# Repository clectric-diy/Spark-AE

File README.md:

Please use these available resources:
- [Canonical Documentation](https://clectric.diy/Spark-AE/)
- [Community Wiki](https://github.com/clectric-diy/Spark-AE/wiki)
- [clectric.diy Discussions](https://github.com/orgs/clectric-diy/discussions)

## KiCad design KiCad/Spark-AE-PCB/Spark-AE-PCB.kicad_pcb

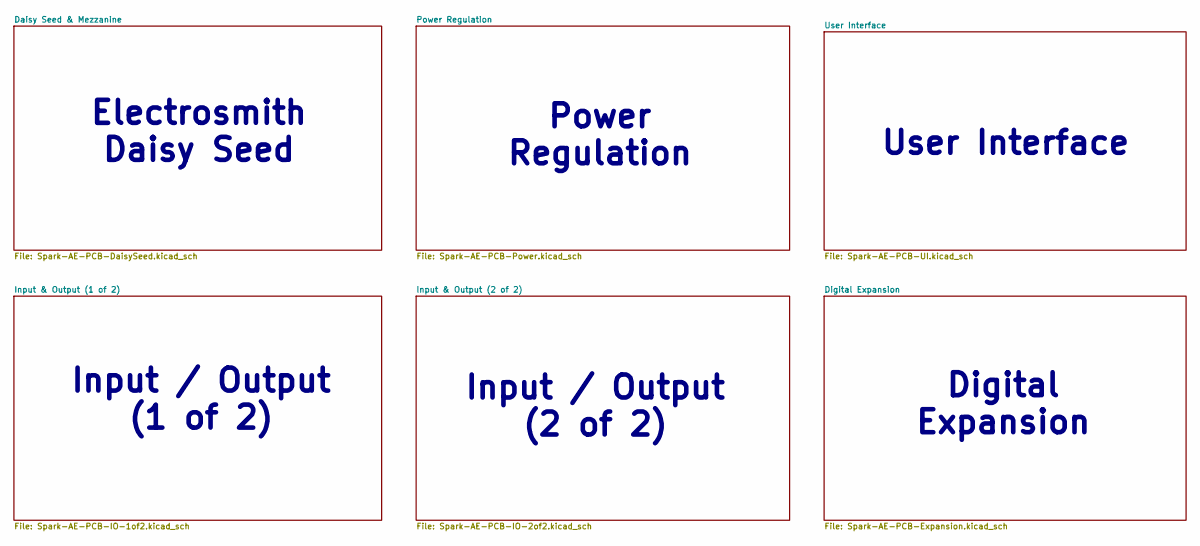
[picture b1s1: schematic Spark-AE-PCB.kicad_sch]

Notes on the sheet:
Input / Output (2 of 2)
Digital Expansion
User Interface
Input / Output (1 of 2)
Power Regulation
Electrosmith Daisy Seed

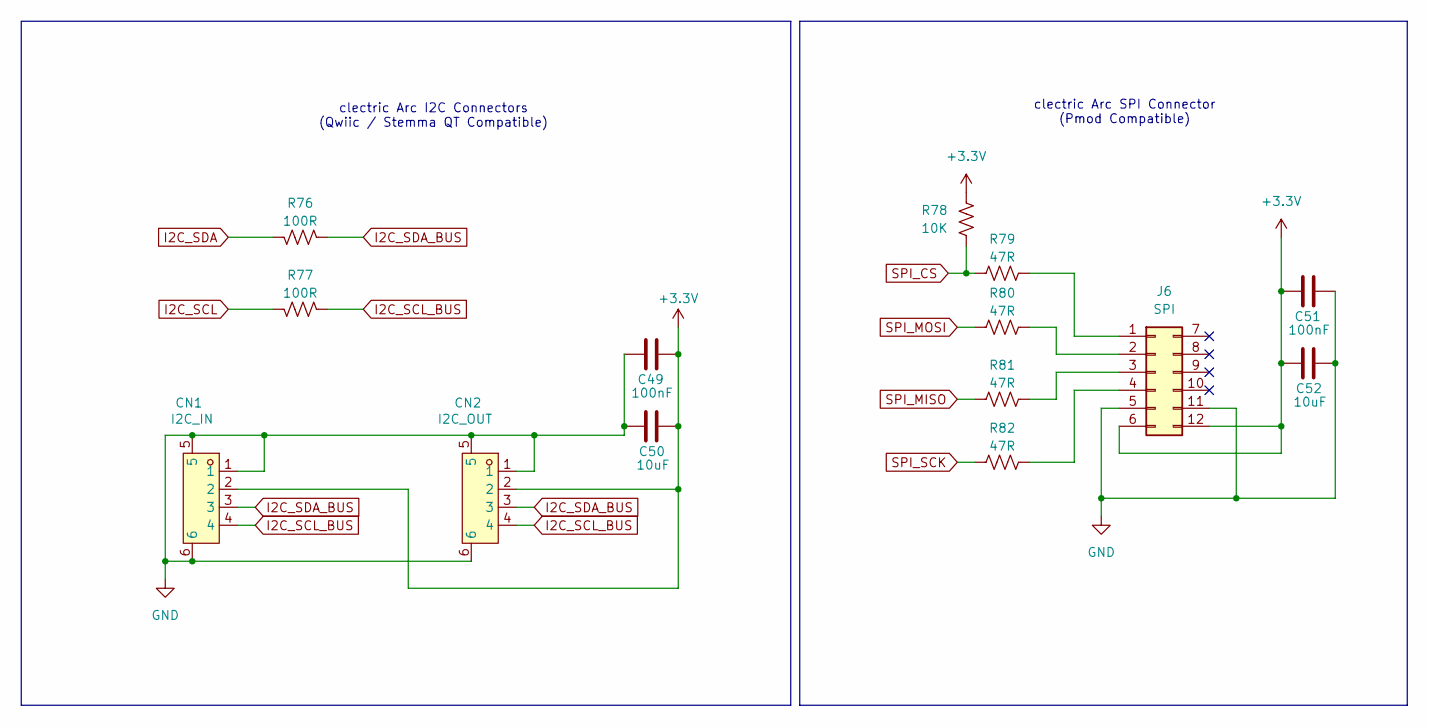
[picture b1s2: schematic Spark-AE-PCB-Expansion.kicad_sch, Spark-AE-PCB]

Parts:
C49, C51: 100nF; C_0603_1608Metric
C50, C52: 10uF; C_0603_1608Metric
CN1: I2C_IN; Connector_JST_BM04B-SRSS-TBT-LF-SN; LCSC Part C495539
CN2: I2C_OUT; Connector_JST_BM04B-SRSS-TBT-LF-SN; LCSC Part C495539
J6: SPI; PinHeader_2x06_P2.54mm_Vertical
R76, R77: 100R; R_0603_1608Metric
R78: 10K; R_0603_1608Metric
R79, R80, R81, R82: 47R; R_0603_1608Metric

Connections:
+3.3V: C49.2, C50.2, C51.1, C52.1, CN1.2, CN2.2, J6.6, J6.12, R78.1; also elsewhere on the board
GND: C49.1, C50.1, C51.2, C52.2, CN1.1, CN1.5, CN1.6, CN2.1, CN2.5, CN2.6, J6.5, J6.11; also elsewhere on the board
I2C_SCL: R77.2; also elsewhere on the board
I2C_SCL_BUS: CN1.4, CN2.4, R77.1
I2C_SDA: R76.2; also elsewhere on the board
I2C_SDA_BUS: CN1.3, CN2.3, R76.1
unnamed: J6.1, R79.2
unnamed: J6.2, R80.2
unnamed: J6.3, R81.2
unnamed: J6.4, R82.2
SPI_CS: R78.2, R79.1; also elsewhere on the board
SPI_MISO: R81.1; also elsewhere on the board
SPI_MOSI: R80.1; also elsewhere on the board
SPI_SCK: R82.1; also elsewhere on the board

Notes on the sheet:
clectric Arc SPI Connector (Pmod Compatible)
clectric Arc I2C Connectors (Qwiic / Stemma QT Compatible)

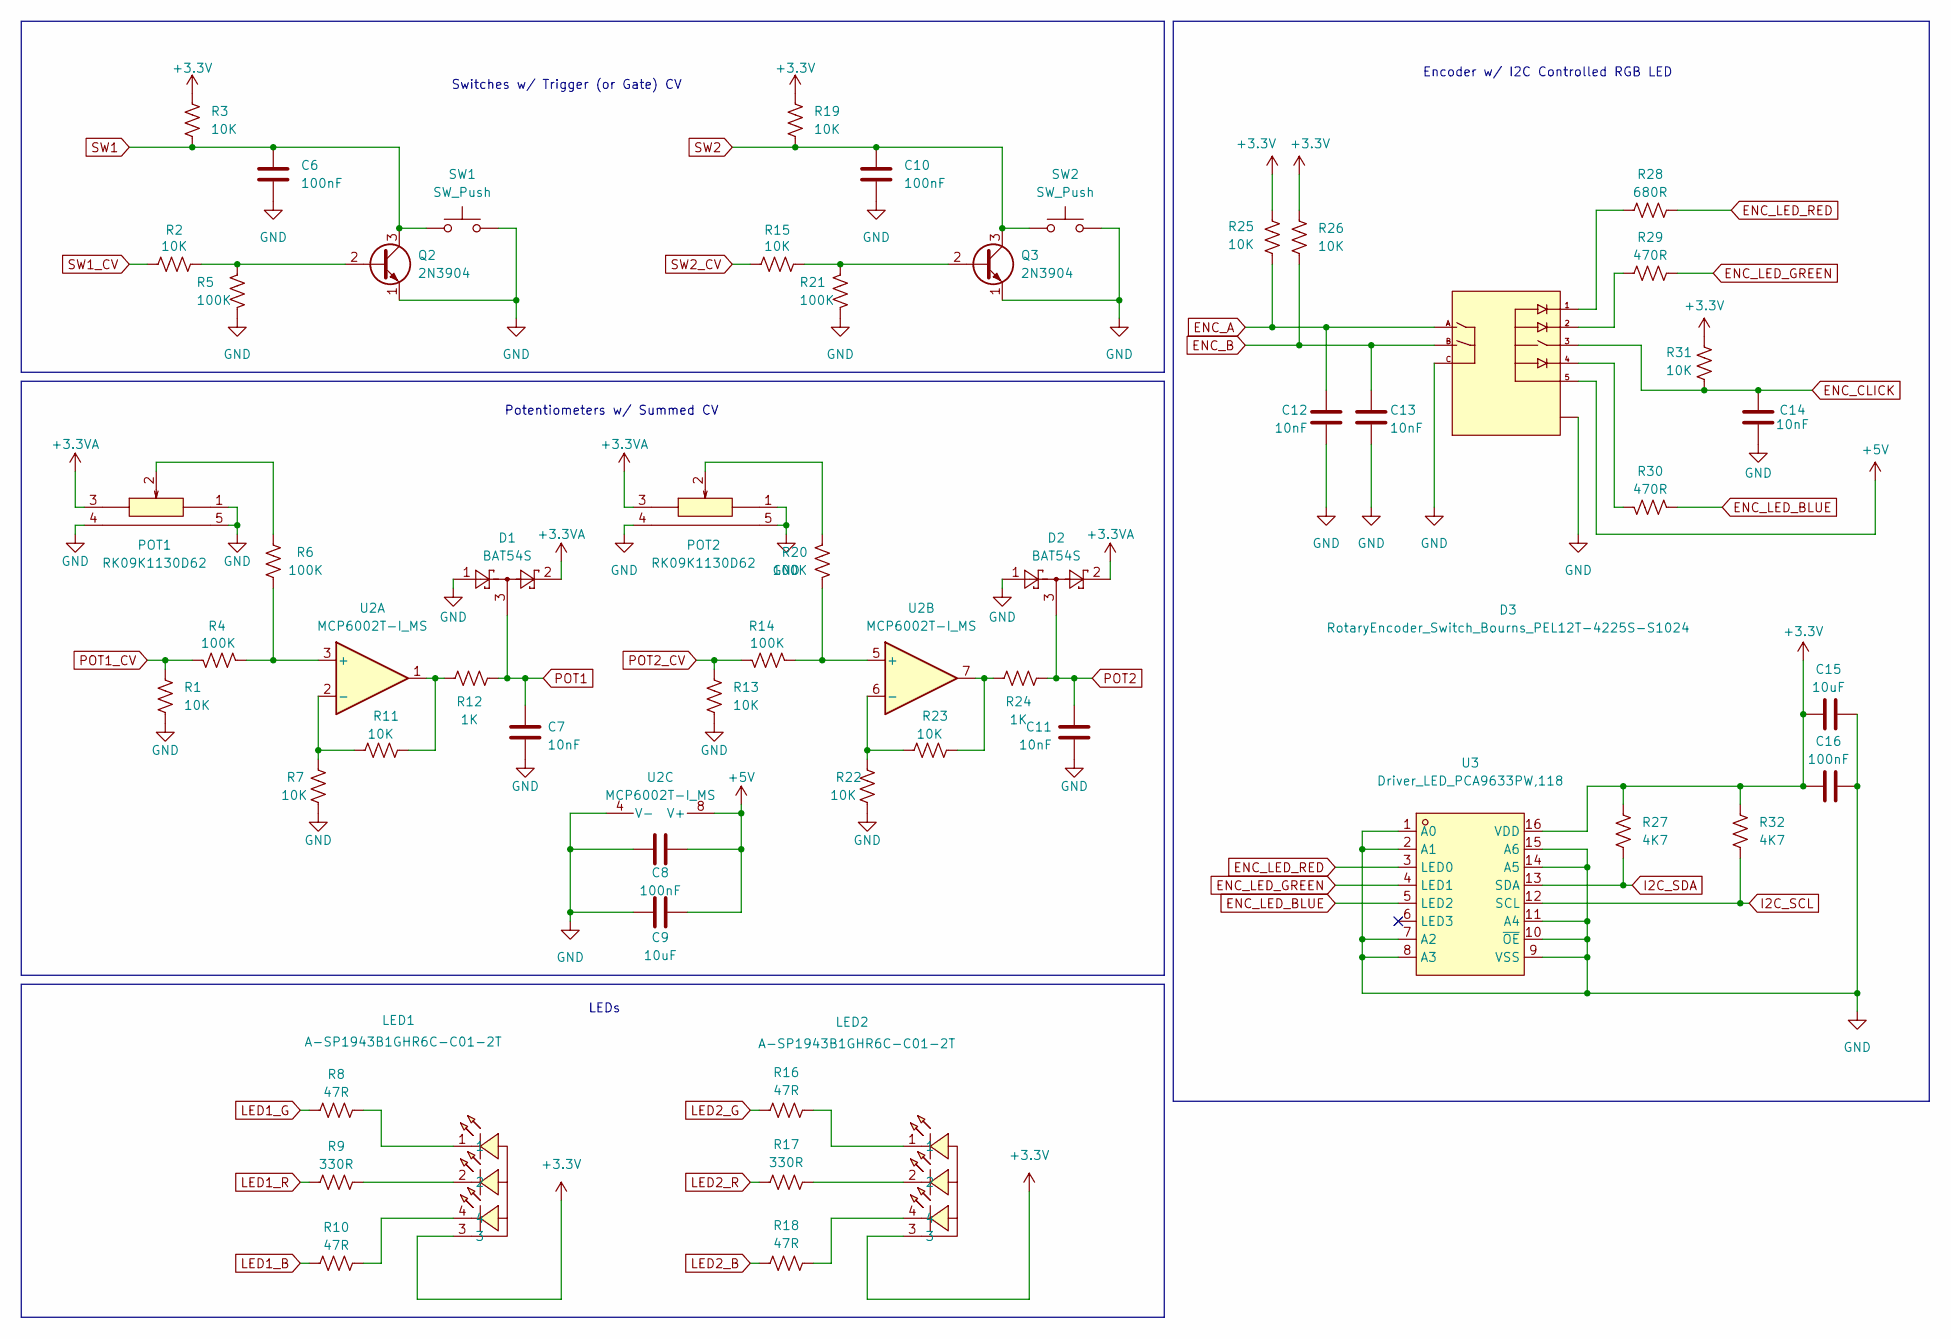
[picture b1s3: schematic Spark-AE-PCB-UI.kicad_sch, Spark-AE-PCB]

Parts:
C6, C8, C10, C16: 100nF; C_0603_1608Metric
C7, C11, C12, C13, C14: 10nF; C_0603_1608Metric
C9, C15: 10uF; C_0603_1608Metric
D1, D2: BAT54S; SOT-23
D3: RotaryEncoder_Switch_Bourns_PEL12T-4225S-S1024; PARTREV N/A
LED1, LED2: A-SP1943B1GHR6C-C01-2T; LED_ARGB_Amicc_A-SP1943B1GHR6C-C01-2T; LCSC Part C19171342
POT1, POT2: RK09K1130D62; Potentiometer_THT_Alps_RK09K1130D62; LCSC Part C470294
Q2, Q3: 2N3904; TO-92_Inline
R1, R2, R3, R7, R11, R13, R15, R19, R22, R23, R25, R26, R31: 10K; R_0603_1608Metric
R4, R5, R6, R14, R20, R21: 100K; R_0603_1608Metric
R8, R10, R16, R18: 47R; R_0603_1608Metric
R9, R17: 330R; R_0603_1608Metric
R12, R24: 1K; R_0603_1608Metric
R27, R32: 4K7; R_0603_1608Metric
R28: 680R; R_0603_1608Metric
R29, R30: 470R; R_0603_1608Metric
SW1, SW2: SW_Push; SW_PUSH_6mm
U2: MCP6002T-I_MS; Amplifier_Operational_Microchip_MCP6002T-I_MS
U3: Driver_LED_PCA9633PW,118; TSSOP-16_L5.0-W4.4-P0.64-LS6.4-BL; LCSC Part C2157802

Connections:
+3.3V: C15.1, C16.1, LED1.3, LED2.3, R3.1, R19.1, R25.1, R26.1, R27.1, R31.1, R32.1, U3.16 (VDD); also elsewhere on the board
+3.3VA: D1.2 (K), D2.2 (K), POT1.3, POT2.3; also elsewhere on the board
+5V: C8.1, C9.2, D3.5, U2.8 (V+); also elsewhere on the board
ENC_A: C12.1, D3.A, R25.2; also elsewhere on the board
ENC_B: C13.1, D3.B, R26.2; also elsewhere on the board
ENC_CLICK: C14.2, D3.3, R31.2; also elsewhere on the board
ENC_LED_BLUE: R30.1, U3.5 (LED2)
ENC_LED_GREEN: R29.2, U3.4 (LED1)
ENC_LED_RED: R28.2, U3.3 (LED0)
GND: C6.2, C7.2, C8.2, C9.1, C10.2, C11.2, C12.2, C13.2, C14.1, C15.2, C16.2, D1.1 (A), D2.1 (A), D3.C, D3.S1 (SHIELD), D3.S2 (SHIELD__1), POT1.1, POT1.4 (EH), POT1.5 (EH), POT2.1, POT2.4 (EH), POT2.5 (EH), Q2.1 (E), Q3.1 (E), R1.2, R5.2, R7.2, R13.2, R21.2, R22.2, SW1.2, SW2.2, U2.4 (V-), U3.1 (A0), U3.2 (A1), U3.7 (A2), U3.8 (A3), U3.9 (VSS), U3.10 (~OE), U3.11 (A4), U3.14 (A5), U3.15 (A6); also elsewhere on the board
I2C_SCL: R32.2, U3.12 (SCL); also elsewhere on the board
I2C_SDA: R27.2, U3.13 (SDA); also elsewhere on the board
LED1_B: R10.1; also elsewhere on the board
LED1_G: R8.1; also elsewhere on the board
LED1_R: R9.1; also elsewhere on the board
LED2_B: R18.1; also elsewhere on the board
LED2_G: R16.1; also elsewhere on the board
LED2_R: R17.1; also elsewhere on the board
unnamed: D3.1, R28.1
unnamed: D3.2, R29.1
unnamed: D3.4, R30.2
unnamed: LED1.1, R8.2
unnamed: LED1.2, R9.2
unnamed: LED1.4, R10.2
unnamed: LED2.1, R16.2
unnamed: LED2.2, R17.2
unnamed: LED2.4, R18.2
unnamed: POT1.2, R6.1
unnamed: POT2.2, R20.1
unnamed: Q2.2 (B), R2.2, R5.1
unnamed: Q3.2 (B), R15.2, R21.1
unnamed: R11.2, R12.1, U2.1
unnamed: R23.2, R24.1, U2.7
unnamed: R4.1, R6.2, U2.3 (+)
unnamed: R7.1, R11.1, U2.2 (-)
unnamed: R14.1, R20.2, U2.5 (+)
unnamed: R22.1, R23.1, U2.6 (-)
POT1: C7.1, D1.3 (COM), R12.2; also elsewhere on the board
POT1_CV: R1.1, R4.2; also elsewhere on the board
POT2: C11.1, D2.3 (COM), R24.2; also elsewhere on the board
POT2_CV: R13.1, R14.2; also elsewhere on the board
SW1: C6.1, Q2.3 (C), R3.2, SW1.1; also elsewhere on the board
SW1_CV: R2.1; also elsewhere on the board
SW2: C10.1, Q3.3 (C), R19.2, SW2.1; also elsewhere on the board
SW2_CV: R15.1; also elsewhere on the board

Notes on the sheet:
LEDs
Encoder w/ I2C Controlled RGB LED
Switches w/ Trigger (or Gate) CV
Potentiometers w/ Summed CV

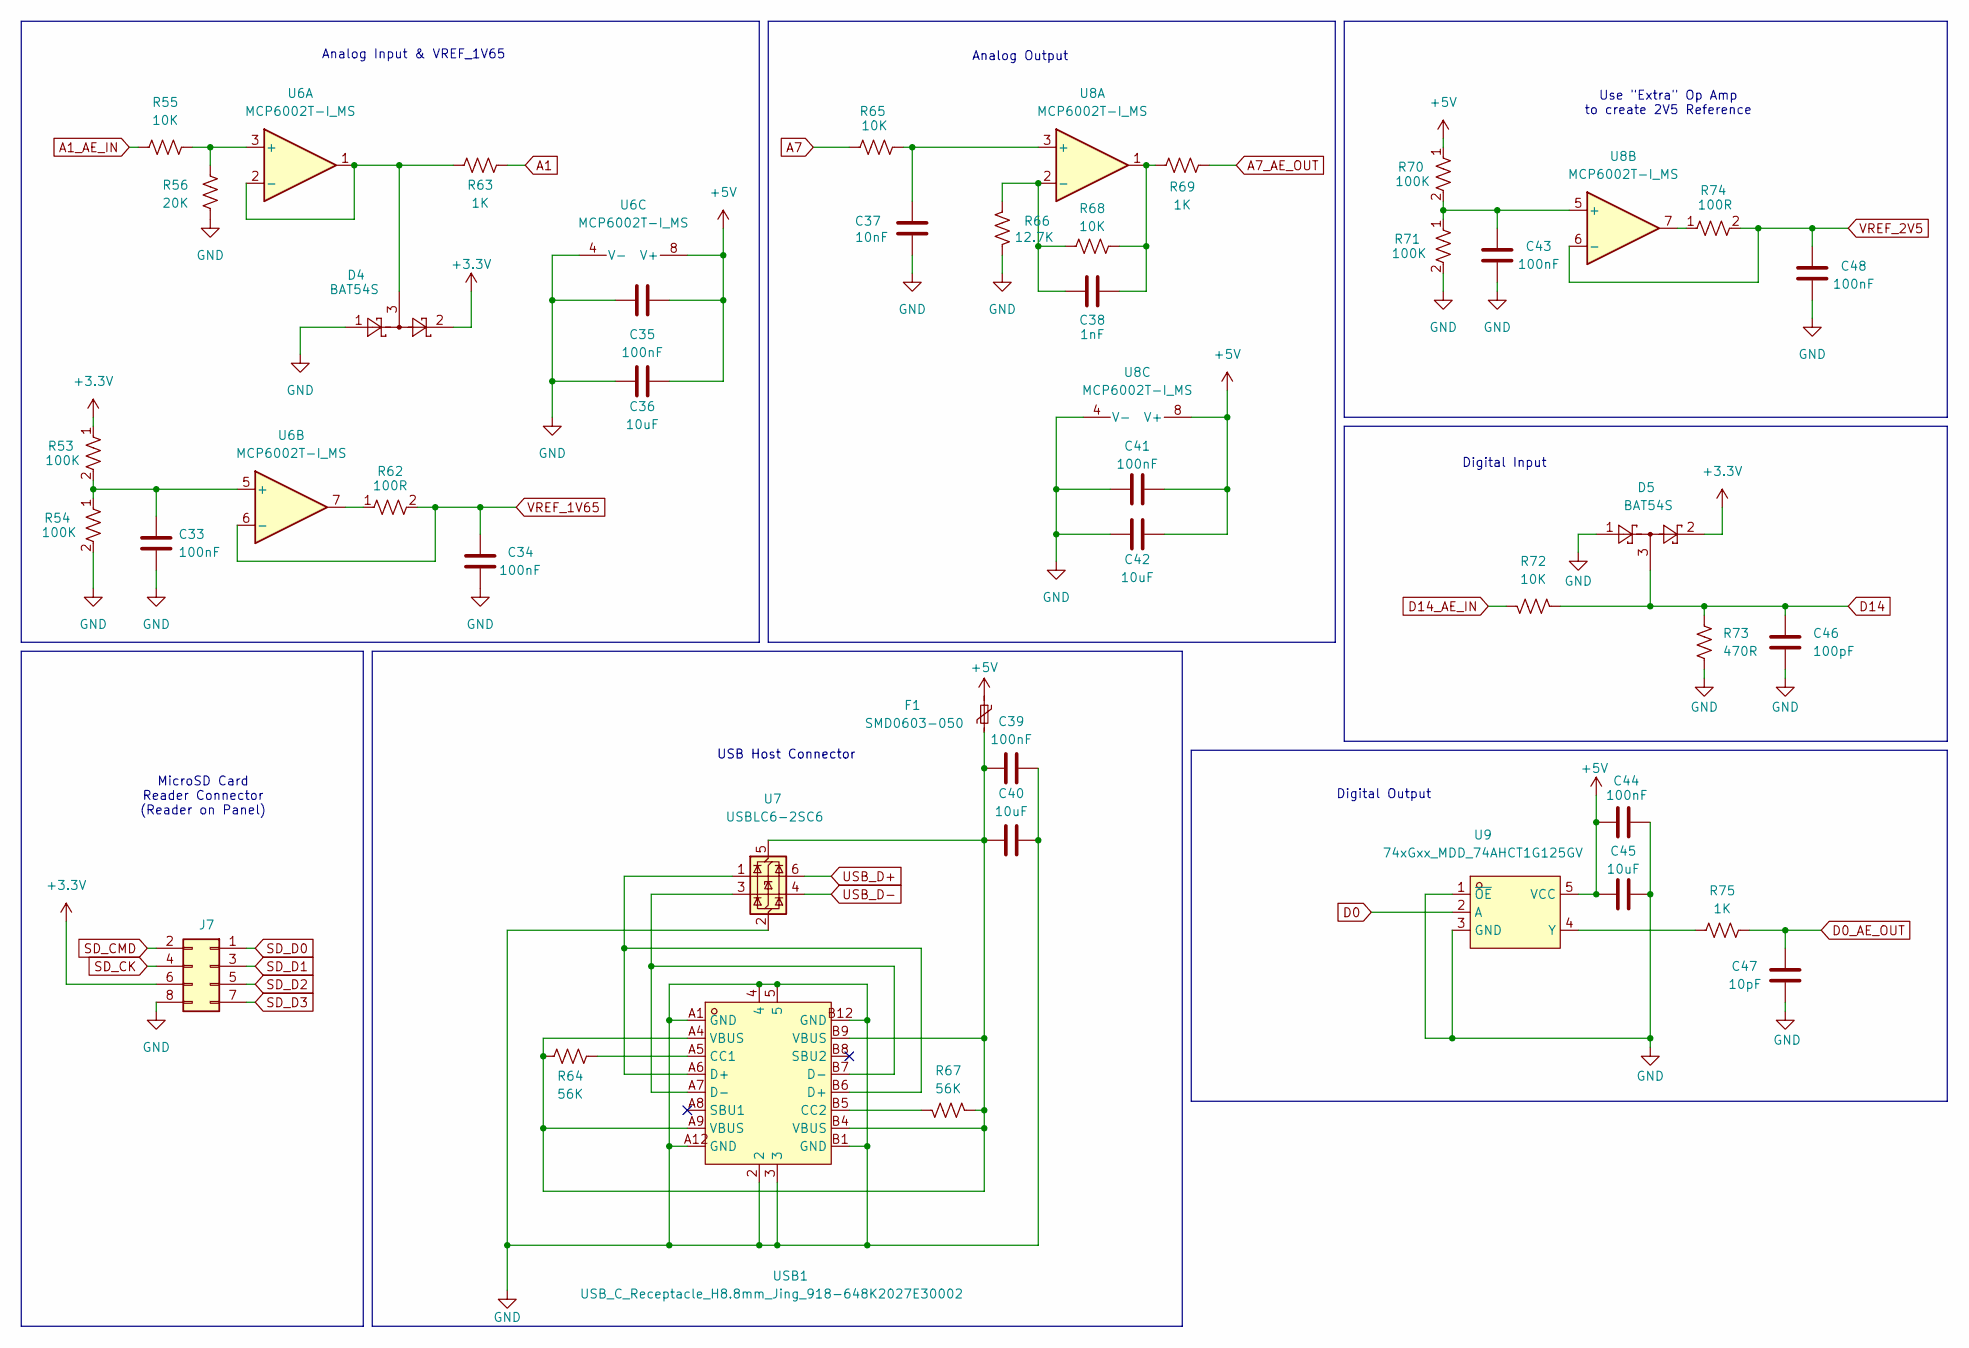
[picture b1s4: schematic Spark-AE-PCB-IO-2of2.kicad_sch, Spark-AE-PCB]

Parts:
C33, C34, C35, C39, C41, C43, C44, C48: 100nF; C_0603_1608Metric
C36, C40, C42, C45: 10uF; C_0603_1608Metric
C37: 10nF; C_0603_1608Metric
C38: 1nF; C_0603_1608Metric
C46: 100pF; C_0603_1608Metric
C47: 10pF; C_0603_1608Metric
D4, D5: BAT54S; SOT-23
F1: SMD0603-050; Fuse_0603_1608Metric
J7: SD_CONN; PinSocket_2x04_P2.54mm_Vertical
R53, R54, R70, R71: 100K; R_0603_1608Metric
R55, R65, R68, R72: 10K; R_0603_1608Metric
R56: 20K; R_0603_1608Metric
R62, R74: 100R; R_0603_1608Metric
R63, R69, R75: 1K; R_0603_1608Metric
R64, R67: 56K; R_0603_1608Metric
R66: 12.7K; R_0603_1608Metric
R73: 470R; R_0603_1608Metric
U6, U8: MCP6002T-I_MS; Amplifier_Operational_Microchip_MCP6002T-I_MS
U7: USBLC6-2SC6; SOT-23-6
U9: 74xGxx_MDD_74AHCT1G125GV; LCSC Part C52140417
USB1: USB_C_Receptacle_H8.8mm_Jing_918-648K2027E30002; LCSC Part C5139026

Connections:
+3.3V: D4.2 (K), D5.2 (K), J7.6, R53.1; also elsewhere on the board
+5V: C35.2, C36.2, C41.2, C42.2, C44.1, C45.2, F1.1, R70.1, U6.8 (V+), U8.8 (V+), U9.5 (VCC); also elsewhere on the board
A1: R63.2; also elsewhere on the board
A1_AE_IN: R55.1; also elsewhere on the board
A7: R65.1; also elsewhere on the board
A7_AE_OUT: R69.2; also elsewhere on the board
D0: U9.2 (A); also elsewhere on the board
D0_AE_OUT: C47.1, R75.1; also elsewhere on the board
D14: C46.1, D5.3 (COM), R72.2, R73.1; also elsewhere on the board
D14_AE_IN: R72.1; also elsewhere on the board
GND: C33.2, C34.2, C35.1, C36.1, C37.2, C39.2, C40.2, C41.1, C42.1, C43.2, C44.2, C45.1, C46.2, C47.2, C48.1, D4.1 (A), D5.1 (A), J7.8, R54.2, R56.2, R66.1, R71.2, R73.2, U6.4 (V-), U7.2 (GND), U8.4 (V-), U9.1 (~OE), U9.3 (GND), USB1.2, USB1.3, USB1.4, USB1.5, USB1.A1 (GND), USB1.A12 (GND), USB1.B1 (GND), USB1.B12 (GND); also elsewhere on the board
unnamed: C38.1, R68.2, R69.1, U8.1
unnamed: D4.3 (COM), R63.1, U6.1, U6.2 (-)
unnamed: R62.1, U6.7
unnamed: R74.1, U8.7
unnamed: R55.2, R56.1, U6.3 (+)
unnamed: C33.1, R53.2, R54.1, U6.5 (+)
unnamed: U7.1 (I/O1), USB1.A6 (D+), USB1.B6 (D+)
unnamed: U7.3 (I/O2), USB1.A7 (D-), USB1.B7 (D-)
unnamed: C39.1, C40.1, F1.2, R64.1, R67.1, U7.5 (VBUS), USB1.A4 (VBUS), USB1.A9 (VBUS), USB1.B4 (VBUS), USB1.B9 (VBUS)
unnamed: C37.1, R65.2, U8.3 (+)
unnamed: C38.2, R66.2, R68.1, U8.2 (-)
unnamed: C43.1, R70.2, R71.1, U8.5 (+)
unnamed: R75.2, U9.4 (Y)
unnamed: R64.2, USB1.A5 (CC1)
unnamed: R67.2, USB1.B5 (CC2)
SD_CK: J7.4; also elsewhere on the board
SD_CMD: J7.2; also elsewhere on the board
SD_D0: J7.1; also elsewhere on the board
SD_D1: J7.3; also elsewhere on the board
SD_D2: J7.5; also elsewhere on the board
SD_D3: J7.7; also elsewhere on the board
USB_D+: U7.6 (I/O1); also elsewhere on the board
USB_D-: U7.4 (I/O2); also elsewhere on the board
VREF_1V65: C34.1, R62.2, U6.6 (-); also elsewhere on the board
VREF_2V5: C48.2, R74.2, U8.6 (-); also elsewhere on the board

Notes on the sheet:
Analog Input & VREF_1V65
MicroSD Card Reader Connector (Reader on Panel)
Analog Output
Digital Input
USB Host Connector
Digital Output
Use "Extra" Op Amp to create 2V5 Reference

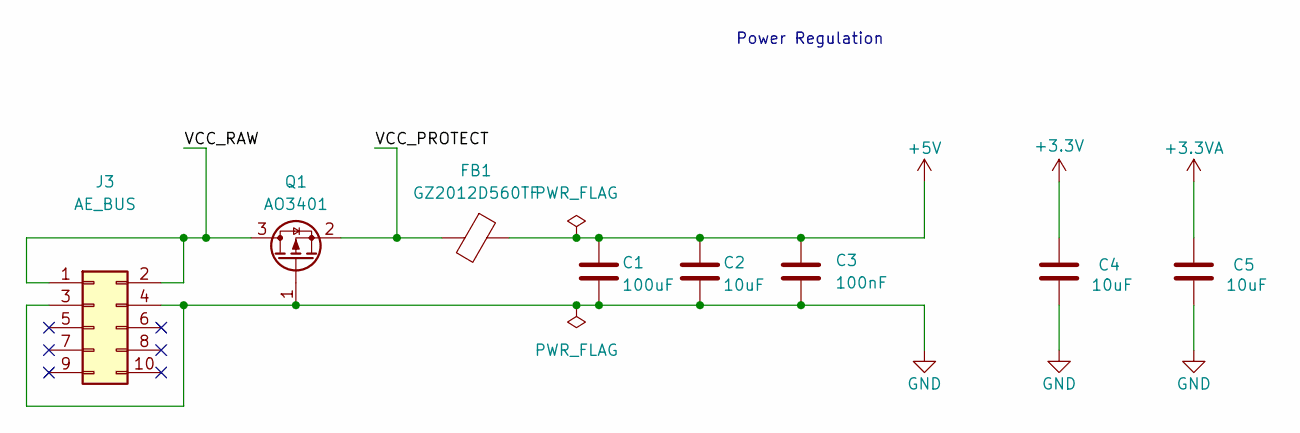
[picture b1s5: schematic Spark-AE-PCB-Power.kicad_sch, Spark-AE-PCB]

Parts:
C1: 100uF; C_0805_2012Metric
C2: 10uF; C_0805_2012Metric
C3: 100nF; C_0805_2012Metric
C4, C5: 10uF; C_0603_1608Metric
FB1: GZ2012D560TF; L_0805_2012Metric
J3: AE_BUS; PinHeader_2x05_P2.54mm_Vertical
Q1: AO3401; SOT-23

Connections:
+3.3V: C4.2; also elsewhere on the board
+3.3VA: C5.2; also elsewhere on the board
+5V: C1.1, C2.1, C3.1, FB1.1; also elsewhere on the board
/Power Regulation/VCC_PROTECT: FB1.2, Q1.2 (S)
/Power Regulation/VCC_RAW: J3.1, J3.2, Q1.3 (D)
GND: C1.2, C2.2, C3.2, C4.1, C5.1, J3.3, J3.4, Q1.1 (G); also elsewhere on the board

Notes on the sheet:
Power Regulation

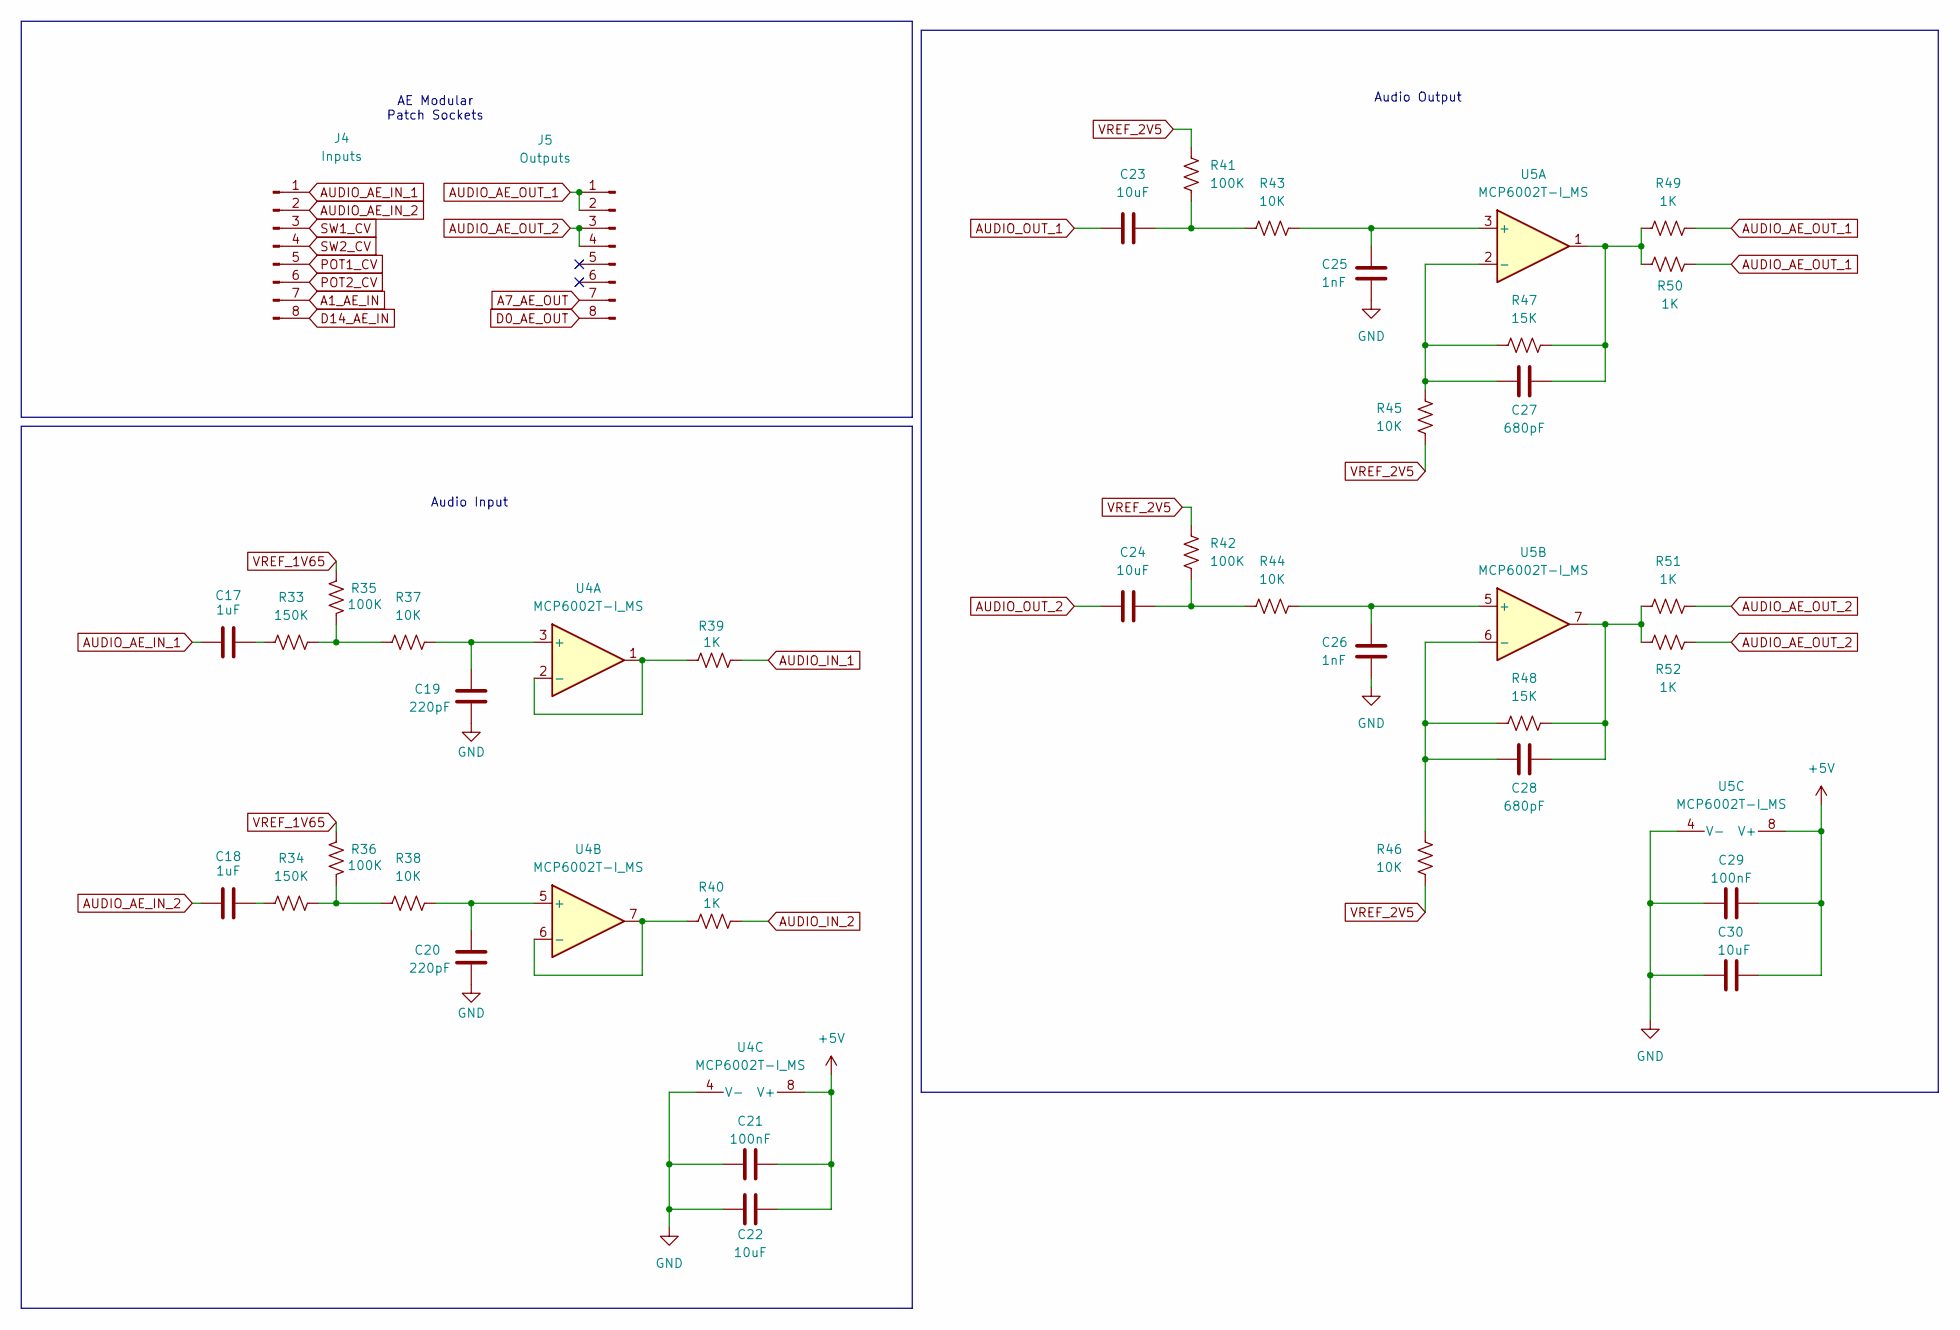
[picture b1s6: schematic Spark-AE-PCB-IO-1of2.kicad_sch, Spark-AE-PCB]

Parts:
C17, C18: 1uF; C_0603_1608Metric
C19, C20: 220pF; C_0603_1608Metric
C21, C29: 100nF; C_0603_1608Metric
C22, C23, C24, C30: 10uF; C_0603_1608Metric
C25, C26: 1nF; C_0603_1608Metric
C27, C28: 680pF; C_0603_1608Metric
J4: Inputs; Connector_PinSocket-1x08-P2.54mm-H8.5mm_Preci-Dip_801-87-00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
J5: Outputs; Connector_PinSocket-1x08-P2.54mm-H8.5mm_Preci-Dip_801-87-00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
R33, R34: 150K; R_0603_1608Metric
R35, R36, R41, R42: 100K; R_0603_1608Metric
R37, R38, R43, R44, R45, R46: 10K; R_0603_1608Metric
R39, R40, R49, R50, R51, R52: 1K; R_0603_1608Metric
R47, R48: 15K; R_0603_1608Metric
U4, U5: MCP6002T-I_MS; Amplifier_Operational_Microchip_MCP6002T-I_MS

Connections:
+5V: C21.2, C22.2, C29.2, C30.1, U4.8 (V+), U5.8 (V+); also elsewhere on the board
A1_AE_IN: J4.7; also elsewhere on the board
A7_AE_OUT: J5.7; also elsewhere on the board
AUDIO_AE_IN_1: C17.1, J4.1
AUDIO_AE_IN_2: C18.1, J4.2
AUDIO_AE_OUT_1: J5.1, J5.2, R49.2, R50.2
AUDIO_AE_OUT_2: J5.3, J5.4, R51.2, R52.2
AUDIO_IN_1: R39.1; also elsewhere on the board
AUDIO_IN_2: R40.1; also elsewhere on the board
AUDIO_OUT_1: C23.2; also elsewhere on the board
AUDIO_OUT_2: C24.2; also elsewhere on the board
D0_AE_OUT: J5.8; also elsewhere on the board
D14_AE_IN: J4.8; also elsewhere on the board
GND: C19.2, C20.2, C21.1, C22.1, C25.2, C26.2, C29.1, C30.2, U4.4 (V-), U5.4 (V-); also elsewhere on the board
unnamed: C17.2, R33.1
unnamed: C18.2, R34.1
unnamed: C23.1, R41.2, R43.1
unnamed: C24.1, R42.2, R44.1
unnamed: C27.1, R47.2, R49.1, R50.1, U5.1
unnamed: C28.1, R48.2, R51.1, R52.1, U5.7
unnamed: R33.2, R35.1, R37.1
unnamed: R34.2, R36.1, R38.1
unnamed: C19.1, R37.2, U4.3 (+)
unnamed: R39.2, U4.1, U4.2 (-)
unnamed: C20.1, R38.2, U4.5 (+)
unnamed: R40.2, U4.6 (-), U4.7
unnamed: C25.1, R43.2, U5.3 (+)
unnamed: C27.2, R45.2, R47.1, U5.2 (-)
unnamed: C26.1, R44.2, U5.5 (+)
unnamed: C28.2, R46.2, R48.1, U5.6 (-)
POT1_CV: J4.5; also elsewhere on the board
POT2_CV: J4.6; also elsewhere on the board
SW1_CV: J4.3; also elsewhere on the board
SW2_CV: J4.4; also elsewhere on the board
VREF_1V65: R35.2, R36.2; also elsewhere on the board
VREF_2V5: R41.1, R42.1, R45.1, R46.1; also elsewhere on the board

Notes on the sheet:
Audio Input
Audio Output
AE Modular Patch Sockets

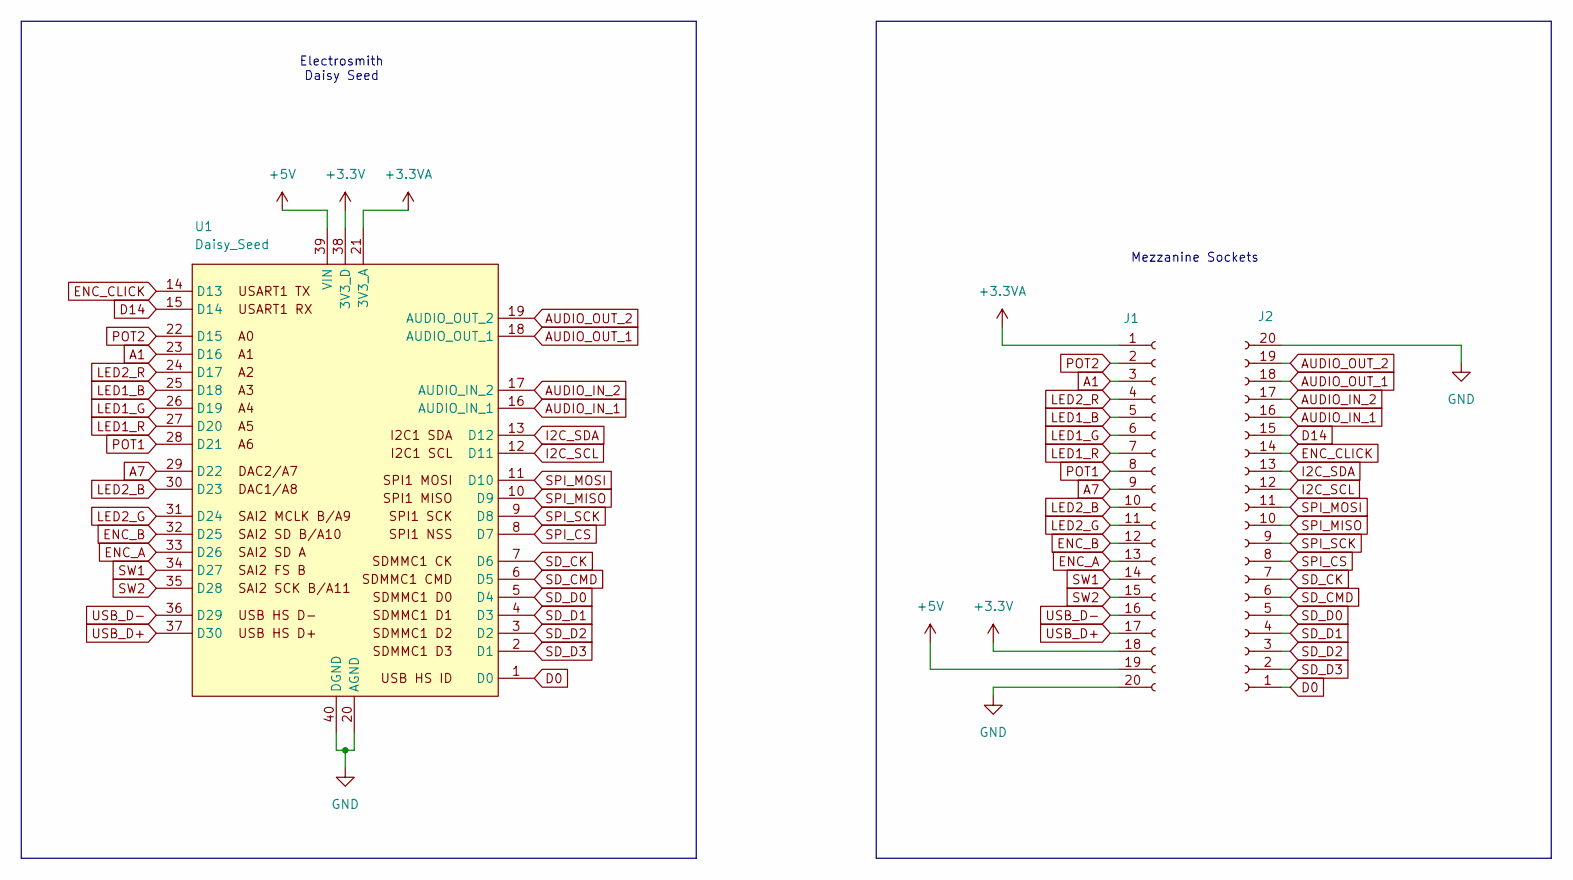
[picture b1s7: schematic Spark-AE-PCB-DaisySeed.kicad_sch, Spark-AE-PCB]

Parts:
J1, J2: Conn_01x20_Socket; Connector_PinSocket-1x20-P2.54mm-H1.27mm_Mill-Max_315-13-12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
U1: Daisy_Seed; MCU_Module_Electrosmith_DAISY_SEED

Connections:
+3.3V: J1.18, U1.38 (3V3_D); also elsewhere on the board
+3.3VA: J1.1, U1.21 (3V3_A); also elsewhere on the board
+5V: J1.19, U1.39 (VIN); also elsewhere on the board
A1: J1.3, U1.23 (D16); also elsewhere on the board
A7: J1.9, U1.29 (D22); also elsewhere on the board
AUDIO_IN_1: J2.16, U1.16 (AUDIO_IN_1); also elsewhere on the board
AUDIO_IN_2: J2.17, U1.17 (AUDIO_IN_2); also elsewhere on the board
AUDIO_OUT_1: J2.18, U1.18 (AUDIO_OUT_1); also elsewhere on the board
AUDIO_OUT_2: J2.19, U1.19 (AUDIO_OUT_2); also elsewhere on the board
D0: J2.1, U1.1 (D0); also elsewhere on the board
D14: J2.15, U1.15 (D14); also elsewhere on the board
ENC_A: J1.13, U1.33 (D26); also elsewhere on the board
ENC_B: J1.12, U1.32 (D25); also elsewhere on the board
ENC_CLICK: J2.14, U1.14 (D13); also elsewhere on the board
GND: J1.20, J2.20, U1.20 (AGND), U1.40 (DGND); also elsewhere on the board
I2C_SCL: J2.12, U1.12 (D11); also elsewhere on the board
I2C_SDA: J2.13, U1.13 (D12); also elsewhere on the board
LED1_B: J1.5, U1.25 (D18); also elsewhere on the board
LED1_G: J1.6, U1.26 (D19); also elsewhere on the board
LED1_R: J1.7, U1.27 (D20); also elsewhere on the board
LED2_B: J1.10, U1.30 (D23); also elsewhere on the board
LED2_G: J1.11, U1.31 (D24); also elsewhere on the board
LED2_R: J1.4, U1.24 (D17); also elsewhere on the board
POT1: J1.8, U1.28 (D21); also elsewhere on the board
POT2: J1.2, U1.22 (D15); also elsewhere on the board
SD_CK: J2.7, U1.7 (D6); also elsewhere on the board
SD_CMD: J2.6, U1.6 (D5); also elsewhere on the board
SD_D0: J2.5, U1.5 (D4); also elsewhere on the board
SD_D1: J2.4, U1.4 (D3); also elsewhere on the board
SD_D2: J2.3, U1.3 (D2); also elsewhere on the board
SD_D3: J2.2, U1.2 (D1); also elsewhere on the board
SPI_CS: J2.8, U1.8 (D7); also elsewhere on the board
SPI_MISO: J2.10, U1.10 (D9); also elsewhere on the board
SPI_MOSI: J2.11, U1.11 (D10); also elsewhere on the board
SPI_SCK: J2.9, U1.9 (D8); also elsewhere on the board
SW1: J1.14, U1.34 (D27); also elsewhere on the board
SW2: J1.15, U1.35 (D28); also elsewhere on the board
USB_D+: J1.17, U1.37 (D30); also elsewhere on the board
USB_D-: J1.16, U1.36 (D29); also elsewhere on the board

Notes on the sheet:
Mezzanine Sockets
Electrosmith Daisy Seed

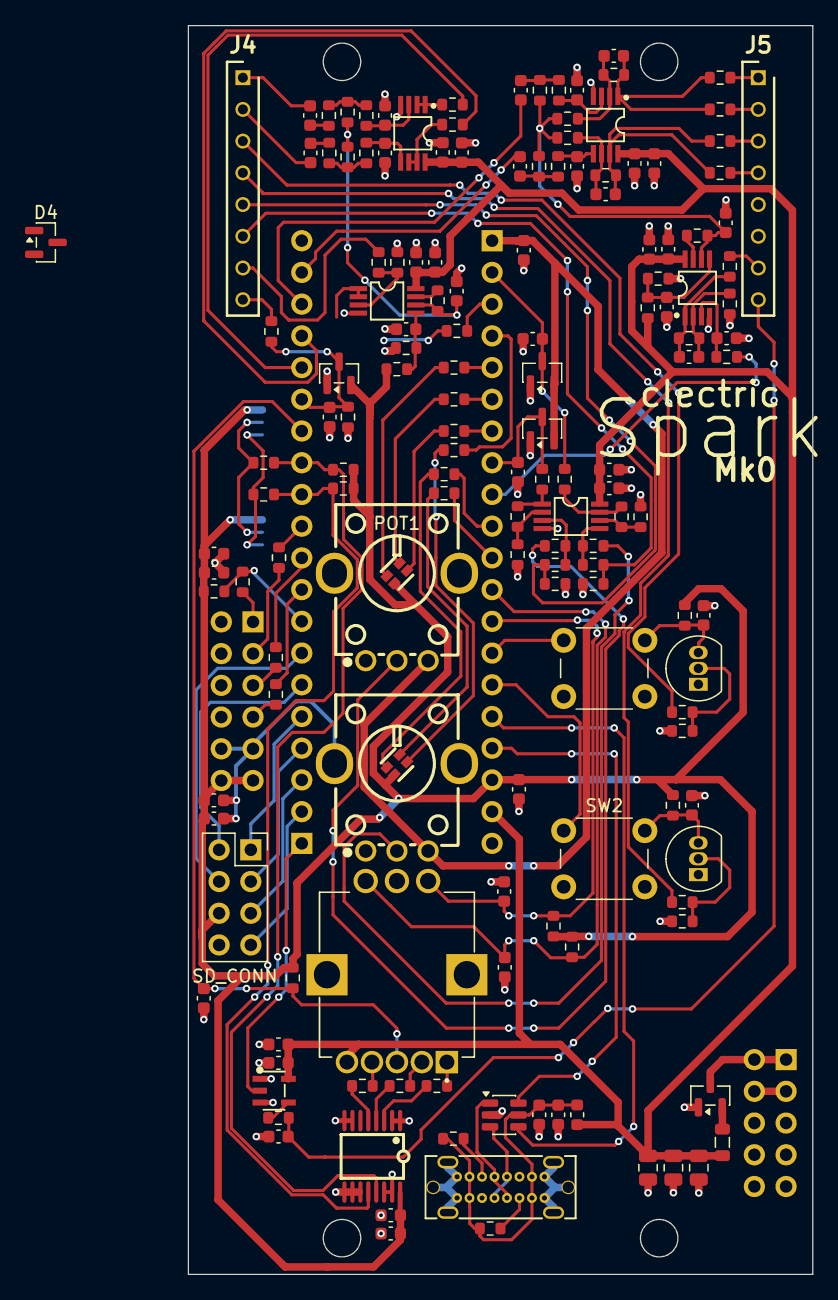
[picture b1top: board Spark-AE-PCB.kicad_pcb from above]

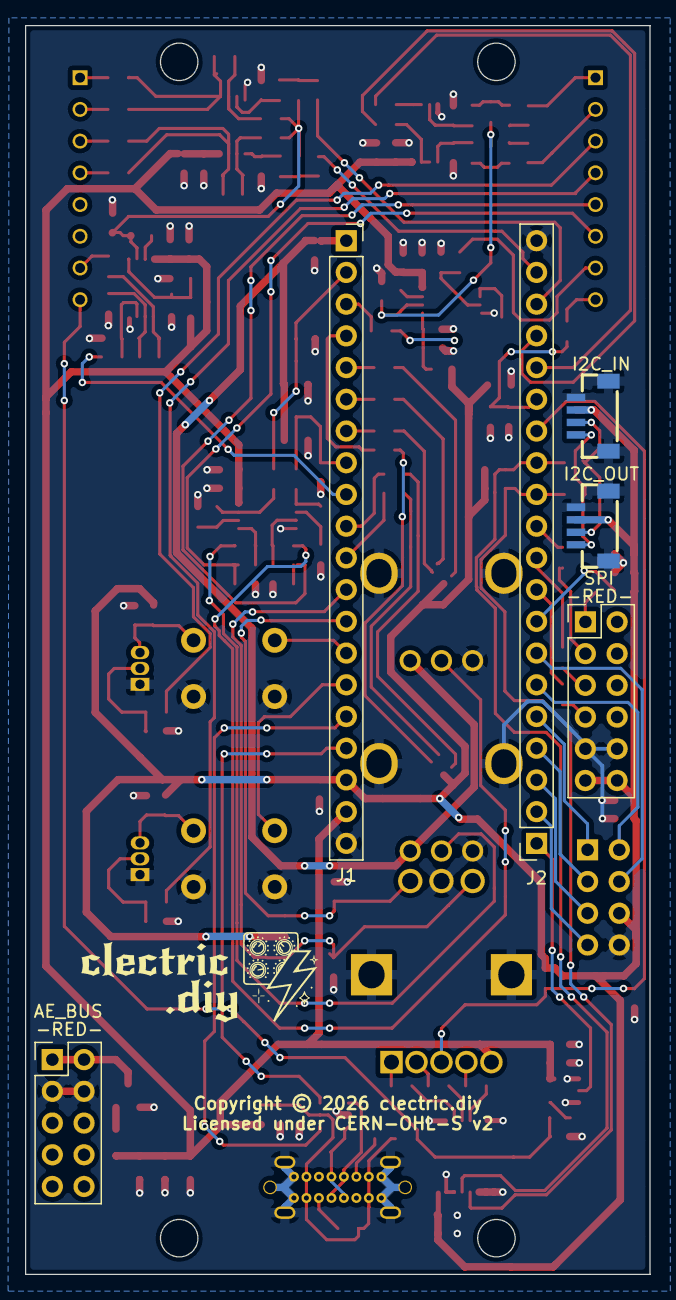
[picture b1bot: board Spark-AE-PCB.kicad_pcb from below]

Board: 2 copper layers, 50.0 x 100.0 mm, 161 parts (6 on the bottom side), 114 nets.

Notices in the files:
KiCad/Spark-AE-PCB/Spark-AE-PCB-DaisySeed.kicad_sch:
Copyright © 2026 clectric.diy Licensed under CERN-OHL-S v2
